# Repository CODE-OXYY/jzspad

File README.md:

# Custom Multi-Purpose Macropad (jzspad)

A multi-purpose macropad featuring 9 customizable LED-backlit keys, 1 rotary encoder, and an OLED display. Powered by the Seeed Studio XIAO RP2040, The keys change depending on the program, but for now they are copy, paste, undo, mute, cam off, close tab, play / pause, screenshot, and most important- show Desktop :)

## 🛠️ Hardware & PCB Design
## SCHEMATIC

The schematic was designed using KiCad all peripherals (OLED, LEDs, Encoder, Matrix) fit perfectly within the 11 available GPIO pins.

## PCB LAYOUT

Designed at a precise 98mm x 75mm, staying  Under the 100x100mm threshold.

## PCB 3D

## 📦 Mechanical Design (3D Case)
The custom enclosure was modeled in **Onshape**. It features snap-fit or screw-mounted standoffs designed perfectly for the custom PCB layout and keycaps.
## onShape Link- **[View 3D Model on Onshape](https://cad.onshape.com/documents/0e5f4d1caed17afff98262ba/w/1524feb8a85fbf17300e4cda/e/ec6d6c9958024086a6d99712)**

## PLATE MODEL

## BOTTOM CASE MODEL

## JZSPAD CAD MODEL

## JZS PADCAD & PCB MODEL

## ✨ Features
* **Microcontroller:** Seeed Studio XIAO RP2040
* **Inputs:** 3x3 Key Matrix (9 Keys) + 1 Rotary Encoder (Volume/Scroll)
* **Visuals:** 128x32 I2C OLED Display for real-time dynamic status updates
* **Lighting:** 13 SK6812MINI-E RGB LEDs 
* **Firmware:** Event-driven KMK framework (CircuitPython)

### 🛒 Bill of Materials (Hardware Needed)
* **9x** MX-Solderable-1U Switches
* **9x** DSA Keycaps
* **4x** M3x5x4 Heatset inserts
* **4x** M3x16mm screws
* **9x** 1N4148 DO-35 Diodes
* **13x** MX_SK6812MINI-E_REV LEDs
* **1x** 0.91" 128x32 OLED Display
* **1x** EC11 Rotary Encoder
* **1x** Seeed Studio XIAO RP2040
* **1x** 3D Printed Case + 1 3D Printed Plate

---

### Extra stuff
**JZS SZN 2025 THEY KNOW IM COMING**

## 📄 License
This project is open-source and available under the **MIT License**.

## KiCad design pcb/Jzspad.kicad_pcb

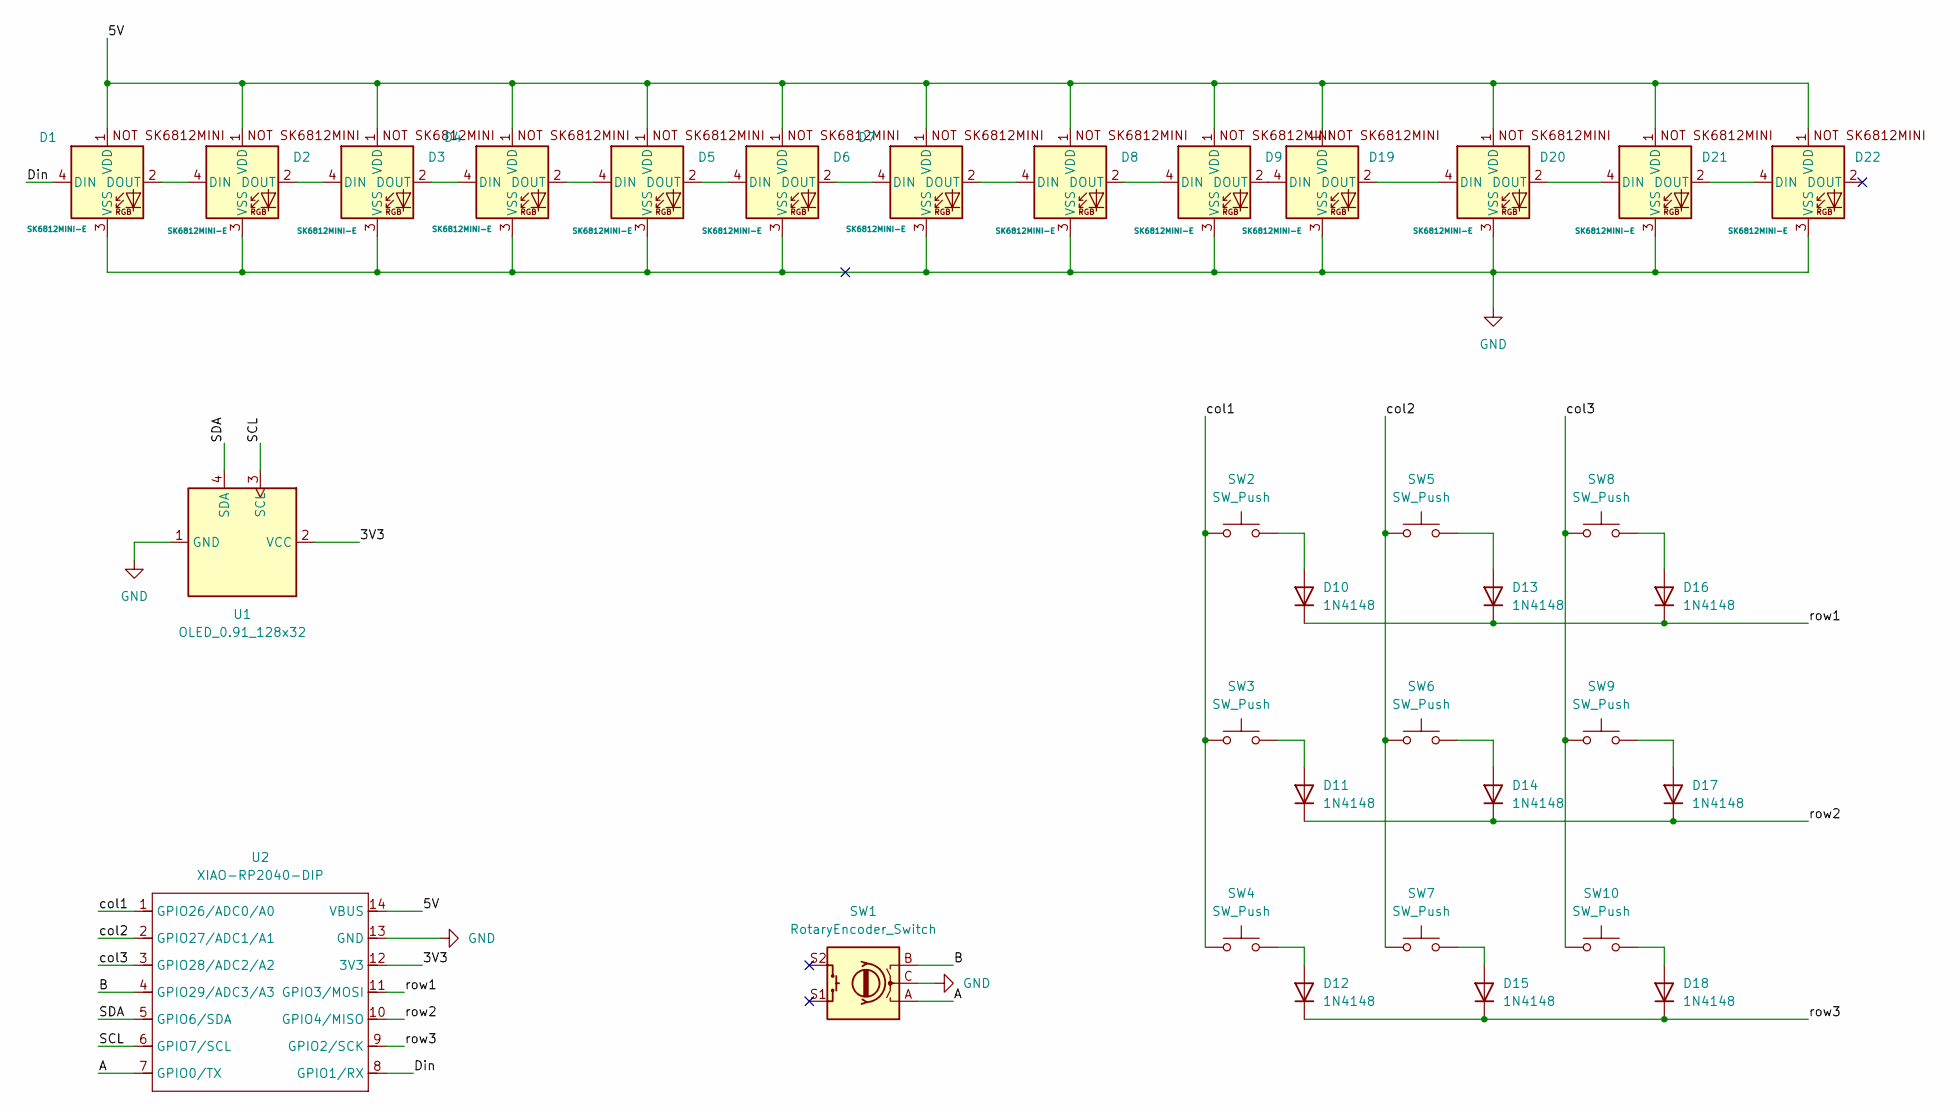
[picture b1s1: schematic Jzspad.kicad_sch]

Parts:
D1, D2, D3, D4, D5, D6, D7, D8, D9, D19, D20, D21, D22: SK6812MINI-E; MX_SK6812MINI-E_REV (1)
D10, D11, D12, D13, D14, D15, D16, D17, D18: 1N4148; D_DO-35_SOD27_P7.62mm_Horizontal
SW1: RotaryEncoder_Switch; RotaryEncoder_Alps_EC11E-Switch_Vertical_H20mm_CircularMoun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
SW2, SW3, SW4, SW5, SW6, SW7, SW8, SW9, SW10: SW_Push; MX-Solderable-1U
U1: OLED_0.91_128x32
U2: XIAO-RP2040-DIP

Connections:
/3V3: U1.2 (VCC), U2.12 (3V3)
/5V: D1.1 (VDD), D2.1 (VDD), D3.1 (VDD), D4.1 (VDD), D5.1 (VDD), D6.1 (VDD), D7.1 (VDD), D8.1 (VDD), D9.1 (VDD), D19.1 (VDD), D20.1 (VDD), D21.1 (VDD), D22.1 (VDD), U2.14 (VBUS)
/A: SW1.A, U2.7 (GPIO0/TX)
/B: SW1.B, U2.4 (GPIO29/ADC3/A3)
/Din: D1.4 (DIN), U2.8 (GPIO1/RX)
/SCL: U1.3 (SCL), U2.6 (GPIO7/SCL)
/SDA: U1.4 (SDA), U2.5 (GPIO6/SDA)
/col1: SW2.1, SW3.1, SW4.1, U2.1 (GPIO26/ADC0/A0)
/col2: SW5.1, SW6.1, SW7.1, U2.2 (GPIO27/ADC1/A1)
/col3: SW8.1, SW9.1, SW10.1, U2.3 (GPIO28/ADC2/A2)
/row1: D10.1 (K), D13.1 (K), D16.1 (K), U2.11 (GPIO3/MOSI)
/row2: D11.1 (K), D14.1 (K), D17.1 (K), U2.10 (GPIO4/MISO)
/row3: D12.1 (K), D15.1 (K), D18.1 (K), U2.9 (GPIO2/SCK)
GND: D1.3 (VSS), D2.3 (VSS), D3.3 (VSS), D4.3 (VSS), D5.3 (VSS), D6.3 (VSS), D7.3 (VSS), D8.3 (VSS), D9.3 (VSS), D19.3 (VSS), D20.3 (VSS), D21.3 (VSS), D22.3 (VSS), SW1.C, U1.1 (GND), U2.13 (GND)
unnamed: D1.2 (DOUT), D2.4 (DIN)
unnamed: D2.2 (DOUT), D3.4 (DIN)
unnamed: D3.2 (DOUT), D4.4 (DIN)
unnamed: D4.2 (DOUT), D5.4 (DIN)
unnamed: D5.2 (DOUT), D6.4 (DIN)
unnamed: D6.2 (DOUT), D7.4 (DIN)
unnamed: D7.2 (DOUT), D8.4 (DIN)
unnamed: D8.2 (DOUT), D9.4 (DIN)
unnamed: D10.2 (A), SW2.2
unnamed: D11.2 (A), SW3.2
unnamed: D12.2 (A), SW4.2
unnamed: D13.2 (A), SW5.2
unnamed: D14.2 (A), SW6.2
unnamed: D15.2 (A), SW7.2
unnamed: D16.2 (A), SW8.2
unnamed: D17.2 (A), SW9.2
unnamed: D18.2 (A), SW10.2
unnamed: D9.2 (DOUT), D19.4 (DIN)
unnamed: D19.2 (DOUT), D20.4 (DIN)
unnamed: D20.2 (DOUT), D21.4 (DIN)
unnamed: D21.2 (DOUT), D22.4 (DIN)

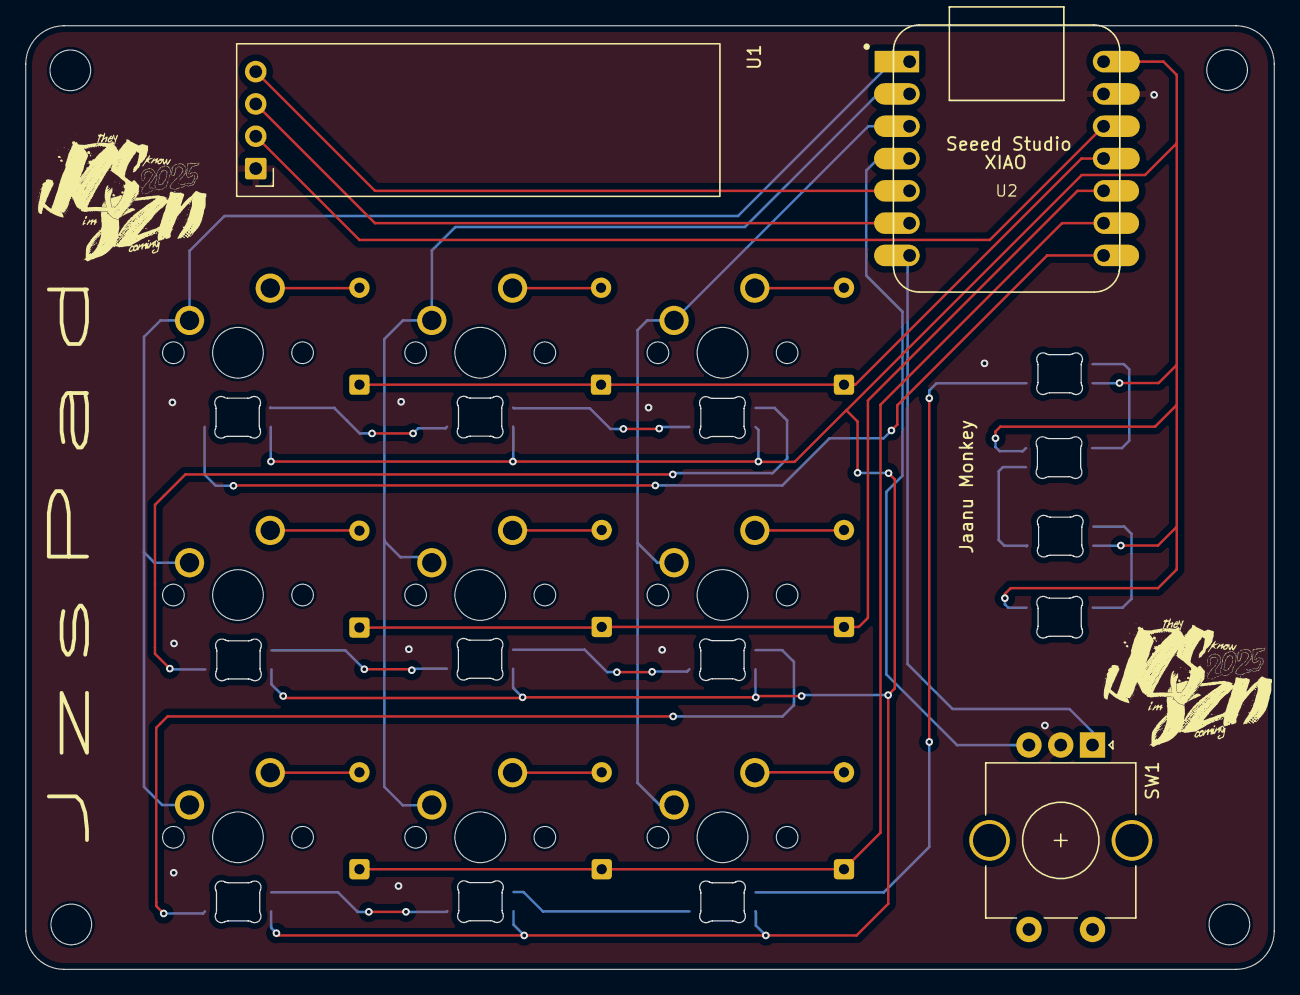
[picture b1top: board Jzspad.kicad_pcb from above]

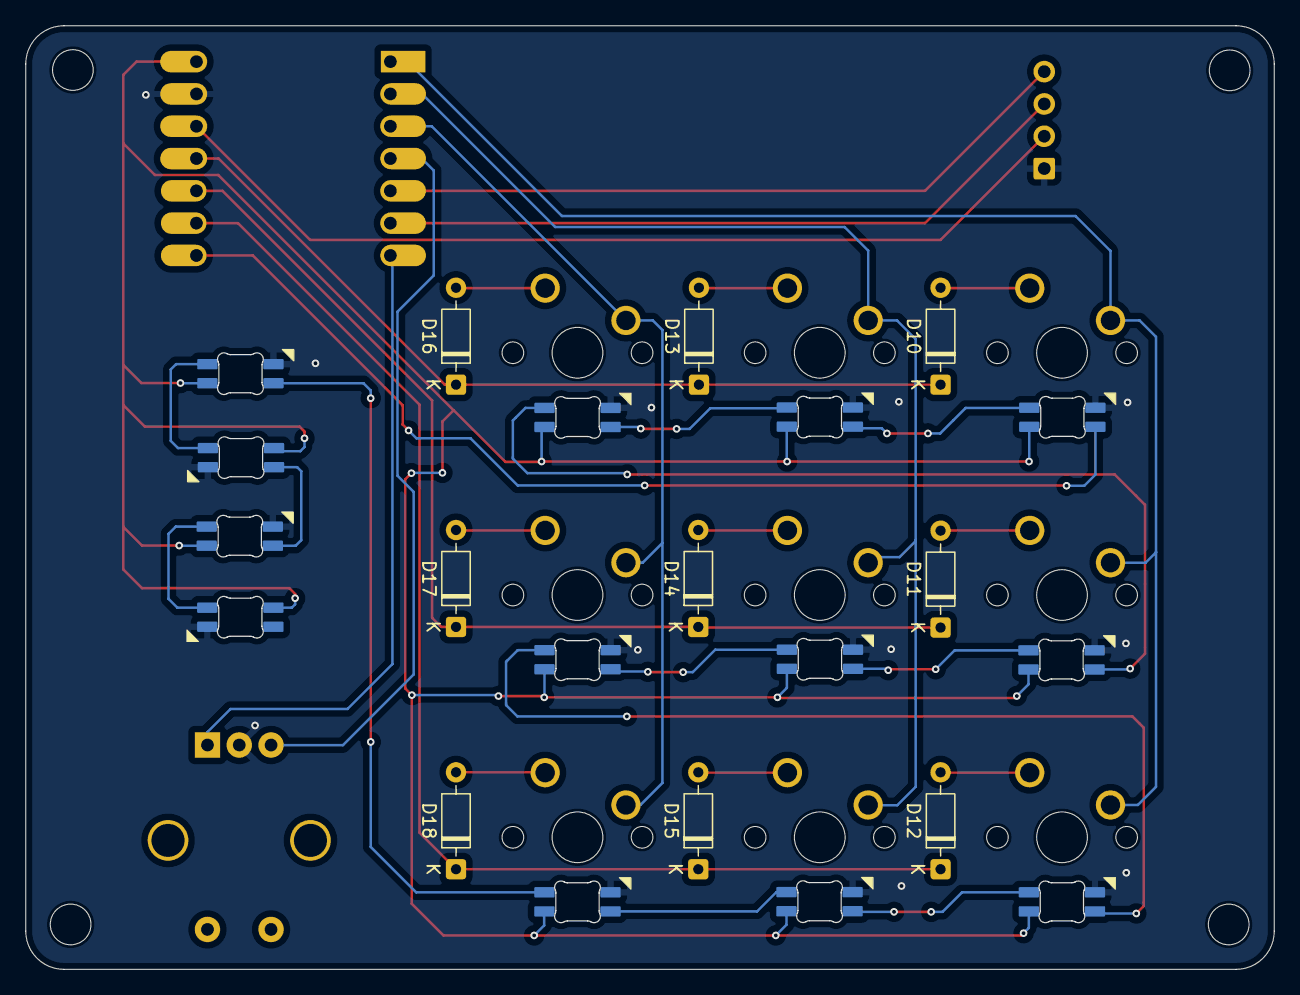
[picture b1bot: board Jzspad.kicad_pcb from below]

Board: 2 copper layers, 98.1 x 74.1 mm, 34 parts (9 on the bottom side), 35 nets.

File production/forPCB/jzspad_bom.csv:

Designator,Footprint,Quantity,Value,LCSC Part #
"D1, D19, D2, D20, D21, D22, D3, D4, D5, D6, D7, D8, D9",MX_SK6812MINI-E_REV (1),13,SK6812MINI-E,
"D10, D11, D12, D13, D14, D15, D16, D17, D18",D_DO-35_SOD27_P7.62mm_Horizontal,9,1N4148,
SW1,RotaryEncoder_Alps_EC11E-Switch_Vertical_H20mm_CircularMountingHoles,1,RotaryEncoder_Switch,
"SW10, SW2, SW3, SW4, SW5, SW6, SW7, SW8, SW9",MX-Solderable-1U,9,SW_Push,
U1,OLED_0.91_128x32,1,OLED_0.91_128x32,
U2,XIAO-Generic-Hybrid-14P-2.54-21X17.8MM,1,XIAO-RP2040-DIP,

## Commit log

2026-03-06 added onshape link
2026-03-06 added whole case step file
2026-03-06 updated stl files
2026-03-06 added bom
2026-03-06 added step files
2026-03-06 Rename bottomcase.step to bottom.step
2026-03-06 Rename Plate.step to plate.step
